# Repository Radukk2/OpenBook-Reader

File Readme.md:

# OpenBook Reader - Project
Block Chart : Block_chart.png file in the root of the directory

Bill of Materials : The bill of materials file can be found at /Manufacturing/Bom.csv

Hardware description
1. Microcontroller - ESP32-C6-WROOM-1-N8
    CPU: 32-bit RISC-V single-core @ up to 160MHz
    Memory: 320KB ROM, 512KB HP SRAM, 16KB LP SRAM
    Connectivity: Wi-Fi 6, Bluetooth LE 5.0
    Interfaces: GPIO, SPI, UART, I2C, PWM   
    Operating Voltage: 3.3V

   - The given microcontroller uses the following power modes: 
        When the device is active it consumes from 160 to 260 mA.
        When modem sleeps it ranges from 3 to 20 mA.
        On light the device consumes 0.8 mA.
        In Deep-sleep mode it consumes 10 μA.
        Hibernation modes consumes 2.5 μA.

2. Display Interface 7.5" E-Paper Display
    - Interface: SPI via FPC connector
    - Pins:   EPD_CS: GPIO10
            EPD_DC: GPIO5
            EPD_RST: GPIO23
            EPD_BUSY: GPIO3
            MOSI, SCK: Shared with SD card
            Used pins : Pins.xlsx  provieds the full ecplination

    The reasons why we use ePaper is for: 
                                        - ultra-low power consumption
                                        - excellent sunlight readability
3. Storage Solutions
    - MicroSD Card with the SPI interface.
    - 64MB NOR Flash with the same SPI interface.

4. Real time clocks
    We use a DS3231SN model for its high accuracy, backup supported battery.

5. Power Management
    USB-C Interface 
    MCP73831 - Li-Po Battery Charging that is used for charging

6. Buttons
    There are also 3 buttons: reset, boot and change. These are used for user's interaction with the device.

Used Pins: Described fully in Pins.xlsx

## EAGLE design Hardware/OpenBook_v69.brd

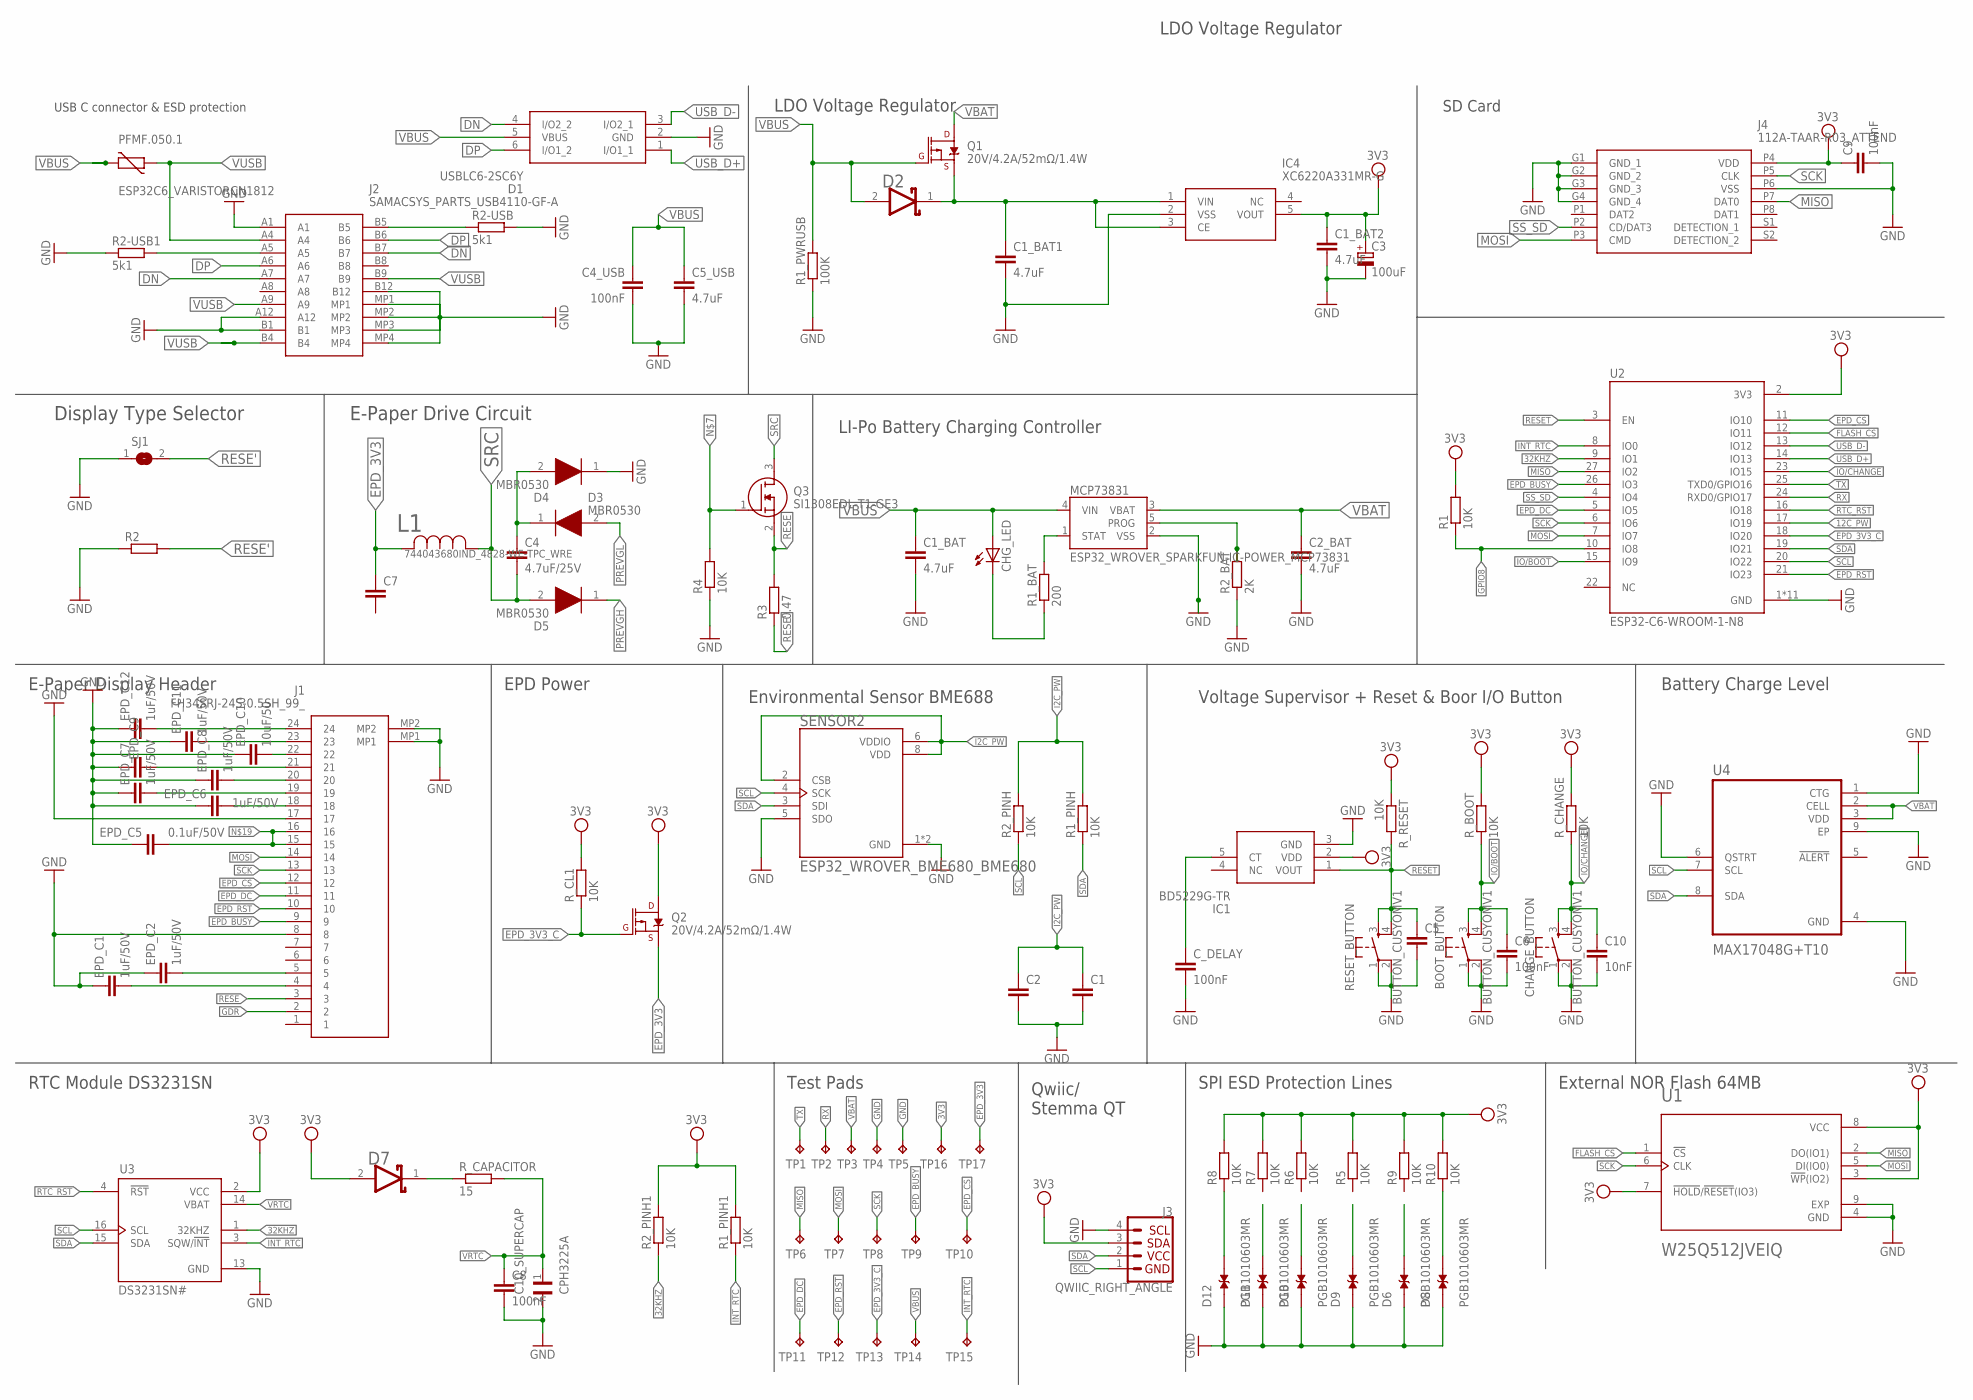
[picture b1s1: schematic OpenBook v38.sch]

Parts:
BOOT_BUTTON: BUTTON_CUSYOMV1; MYBUTTON
C1, C2, C5, C7: EAGLE-LTSPICE_CC0402; EAGLE-LTSPICE_C0402
C1_BAT, C1_BAT1, C1_BAT2, C2_BAT, C5_USB: 4.7uF; EAGLE-LTSPICE_C0402
C3: 100uF; RCL_CT3528
C4: 4.7uF/25V; EAGLE-LTSPICE_C0402
C4_USB, C6, C8, C9: 100nF; EAGLE-LTSPICE_C0402
C10: 10nF; EAGLE-LTSPICE_C0402
C10_SUPERCAP: CPH3225A; CAPCP3225X100N
CHANGE_BUTTON: BUTTON_CUSYOMV1; MYBUTTON
CHG_LED: ADAFRUIT_LEDCHIP-LED0603; ADAFRUIT_CHIP-LED0603
C_DELAY: 100nF; EAGLE-LTSPICE_C0402
D1: USBLC6-2SC6Y; SOT95P280X145-6N
D2, D7: ESP32_WROVER_AVX---SD0805S020S1R0_AVX_SD0805S020S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; ESP32_WROVER_AVX---SD0805S020S1R0_AVX_SD0805S020S1R0_0
D3, D4, D5: MBR0530; SOD3716X135N
D6, D8, D9, D10, D11, D12: PGB1010603MR; DIOC1608X36N
EPD_C1, EPD_C2, EPD_C6, EPD_C7, EPD_C8, EPD_C11, EPD_C12: 1uF/50V; EAGLE-LTSPICE_C0402
EPD_C5: 0.1uF/50V; EAGLE-LTSPICE_C0402
EPD_C9: EAGLE-LTSPICE_CC0402; EAGLE-LTSPICE_C0402
EPD_C10: 10uF/50; EAGLE-LTSPICE_C0402
IC1: BD5229G-TR; SOT95P280X125-5N
IC4: XC6220A331MR-G; SOT95P280X120-5N
J1: FH34SRJ-24S-0.5SH_99_; FH34SRJ24S05SH99
J2: SAMACSYS_PARTS_USB4110-GF-A; SAMACSYS_PARTS_USB4110GFA
J3: QWIIC_RIGHT_ANGLE; JST04_1MM_RA
J4: 112A-TAAR-R03_ATTEND; 112ATAARR03ATTEND
L1: 744043680IND_4828-WE-TPC_WRE; IND_4828-WE-TPC_WRE
MCP73831: ESP32_WROVER_SPARKFUN-IC-POWER_MCP73831; ESP32_WROVER_SPARKFUN-IC-POWER_SOT23-5
PFMF.050.1: ESP32C6_VARISTORCN1812; ESP32C6_VARISTOR_CT/CN1812
Q1, Q2: 20V/4.2A/52mΩ/1.4W; ESP32_WROVER_SPARKFUN-DISCRETESEMI_SOT23-3
Q3: SI1308EDL-T1-GE3; SOT65P210X110-3N
R1, R1_PINH, R1_PINH1, R2_PINH, R2_PINH1, R4, R5, R6, R7, R8, R9, R10: 10K; ESP32_WROVER_EAGLE-LTSPICE_R0402
R1_BAT: 200; ESP32_WROVER_EAGLE-LTSPICE_R0402
R1_PWRUSB: 100K; ESP32_WROVER_EAGLE-LTSPICE_R0402
R2: ESP32_WROVER_EAGLE-LTSPICE_RR0402; ESP32_WROVER_EAGLE-LTSPICE_R0402
R2-USB, R2-USB1: 5k1; ESP32_WROVER_EAGLE-LTSPICE_R0402
R2_BAT: 2K; ESP32_WROVER_EAGLE-LTSPICE_R0402
R3: 0.47; ESP32_WROVER_EAGLE-LTSPICE_R0402
RESET_BUTTON: BUTTON_CUSYOMV1; MYBUTTON
R_BOOT: 10K; ESP32_WROVER_EAGLE-LTSPICE_R0402
R_CAPACITOR: 15; ESP32_WROVER_EAGLE-LTSPICE_R0402
R_CHANGE: 10K; ESP32_WROVER_EAGLE-LTSPICE_R0402
R_CL1: 10K; ESP32_WROVER_EAGLE-LTSPICE_R0402
R_RESET: 10K; ESP32_WROVER_EAGLE-LTSPICE_R0402
SENSOR2: ESP32_WROVER_BME680_BME680; ESP32_WROVER_BME680_PSON80P300X300X100-8N
SJ1: SJ
TP1, TP2, TP3, TP4, TP5, TP6, TP7, TP8, TP9, TP10, TP11, TP12, TP13, TP14, TP15, TP16, TP17: TPTP20R; TP20R
U1: W25Q512JVEIQ; SON127P600X800X80-9N
U2: ESP32-C6-WROOM-1-N8; XCVR_ESP32-C6-WROOM-1-N8
U3: DS3231SN#; SOIC127P1032X265-16N
U4: MAX17048G+T10; SON50P200X200X80-9N

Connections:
3V3: C1_BAT2.1, C3.+, C9.1, D7.2 (ANODE), IC1.2 (VDD), IC4.5 (VOUT), J3.3, J4.P4 (VDD), Q2.3 (D), R1.2, R1_PINH1.2, R2_PINH1.2, R5.2, R6.2, R7.2, R8.2, R9.2, R10.2, R_BOOT.2, R_CHANGE.2, R_CL1.2, R_RESET.1, TP16.TP, U1.3 (!WP!(IO2)), U1.7 (!HOLD!/!RESET!(IO3)), U1.8 (VCC), U2.2 (3V3), U3.2 (VCC)
12C_PW: U2.17 (IO19)
32KHZ: R2_PINH1.1, U2.9 (IO1), U3.1 (32KHZ)
DN: D1.4 (I/O2_2), J2.A7, J2.B7
DP: D1.6 (I/O1_2), J2.A6, J2.B6
EPD_3V3: C7.1, L1.2, Q2.2 (S), TP17.TP
EPD_3V3_C: Q2.1 (G), R_CL1.1, TP13.TP, U2.18 (IO20)
EPD_BUSY: J1.9, TP9.TP, U2.26 (IO3)
EPD_CS: J1.12, TP10.TP, U2.11 (IO10)
EPD_DC: J1.11, TP11.TP, U2.5 (IO5)
EPD_RST: J1.10, TP12.TP, U2.21 (IO23)
FLASH_CS: U1.1 (!CS), U2.12 (IO11)
GDR: J1.2
GND: BOOT_BUTTON.1, BOOT_BUTTON.2, C1.2, C1_BAT.2, C1_BAT1.2, C1_BAT2.2, C2.2, C2_BAT.2, C3.-, C4_USB.2, C5.2, C5_USB.2, C6.2, C8.2, C9.2, C10.2, C10_SUPERCAP.2, CHANGE_BUTTON.1, CHANGE_BUTTON.2, C_DELAY.2, D1.2 (GND), D4.1 (K), D6.1, D8.1, D9.1, D10.1, D11.1, D12.1, EPD_C1.1, EPD_C2.1, EPD_C5.1, EPD_C6.1, EPD_C7.1, EPD_C8.1, EPD_C9.1, EPD_C10.1, EPD_C11.1, EPD_C12.1, IC1.3 (GND), IC4.2 (VSS), J1.8, J1.17, J1.MP1, J1.MP2, J2.A1, J2.A12, J2.B1, J2.B12, J2.MP1, J2.MP2, J2.MP3, J2.MP4, J3.4, J4.G1 (GND_1), J4.G2 (GND_2), J4.G3 (GND_3), J4.G4 (GND_4), J4.P6 (VSS), MCP73831.2 (VSS), R1_PWRUSB.1, R2.1, R2-USB.2, R2-USB1.1, R2_BAT.1, R4.1, RESET_BUTTON.1, RESET_BUTTON.2, SENSOR2.1 (GND), SENSOR2.5 (SDO), SENSOR2.7 (GND), SJ1.1, TP4.TP, TP5.TP, U1.4 (GND), U1.9 (EXP), U2.1 (GND), U2.28 (GND), U2.29_1 (GND), U2.29_2 (GND), U2.29_3 (GND), U2.29_4 (GND), U2.29_5 (GND), U2.29_6 (GND), U2.29_7 (GND), U2.29_8 (GND), U2.29_9 (GND), U3.13 (GND), U4.1 (CTG), U4.4 (GND), U4.6 (QSTRT), U4.9 (EP)
GPIO8: R1.1, U2.10 (IO8)
I2C_PW: C1.1, C2.1, R1_PINH.2, R2_PINH.2, SENSOR2.2 (CSB), SENSOR2.6 (VDDIO), SENSOR2.8 (VDD)
INT_RTC: R1_PINH1.1, TP15.TP, U2.8 (IO0), U3.3 (SQW/!INT)
IO/BOOT: BOOT_BUTTON.3, BOOT_BUTTON.4, C6.1, R_BOOT.1, U2.15 (IO9)
IO/CHANGE: C10.1, CHANGE_BUTTON.3, CHANGE_BUTTON.4, R_CHANGE.1, U2.23 (IO15)
MISO: J4.P7 (DAT0), TP6.TP, U1.2 (DO(IO1)), U2.27 (IO2)
MOSI: J1.14, J4.P3 (CMD), TP7.TP, U1.5 (DI(IO0)), U2.7 (IO7)
unnamed: J2.B5, R2-USB.1
unnamed: J2.A5, R2-USB1.2
unnamed: C1_BAT1.1, D2.1 (CATHODE), IC4.1 (VIN), IC4.3 (CE), Q1.2 (S)
unnamed: C4.1, D3.1 (K), D4.2 (A)
unnamed: MCP73831.5 (PROG), R2_BAT.2
unnamed: Q3.1 (G), R4.2
unnamed: EPD_C1.2, J1.4
unnamed: MCP73831.1 (STAT), R1_BAT.2
unnamed: CHG_LED.C, R1_BAT.1
unnamed: EPD_C2.2, J1.5
unnamed: EPD_C6.2, J1.18
unnamed: EPD_C7.2, J1.19
unnamed: EPD_C8.2, J1.20
unnamed: EPD_C9.2, J1.21
unnamed: EPD_C10.2, J1.22
unnamed: EPD_C12.2, J1.24
unnamed: EPD_C11.2, J1.23
unnamed: EPD_C5.2, J1.15, J1.16
unnamed: C_DELAY.1, IC1.5 (CT)
unnamed: D7.1 (CATHODE), R_CAPACITOR.1
unnamed: D12.2, R8.1
unnamed: D8.2, R10.1
PREVGH: D5.1 (K)
PREVGL: D3.2 (A)
RESE: J1.3, Q3.2 (S), R3.2
RESE': R2.2, R3.1, SJ1.2
RESET: C5.1, IC1.1 (VOUT), RESET_BUTTON.3, RESET_BUTTON.4, R_RESET.2, U2.3 (EN)
RTC_RST: U2.16 (IO18), U3.4 (!RST)
RX: TP2.TP, U2.24 (RXD0/GPIO17)
SCK: J1.13, J4.P5 (CLK), TP8.TP, U1.6 (CLK), U2.6 (IO6)
SCL: J3.1, R2_PINH.1, SENSOR2.4 (SCK), U2.20 (IO22), U3.16 (SCL), U4.7 (SCL)
SDA: J3.2, R1_PINH.1, SENSOR2.3 (SDI), U2.19 (IO21), U3.15 (SDA), U4.8 (SDA)
SRC: C4.2, D5.2 (A), L1.1, Q3.3 (D)
SS_SD: J4.P2 (CD/DAT3), U2.4 (IO4)
TX: TP1.TP, U2.25 (TXD0/GPIO16)
USB_D+: D1.1 (I/O1_1), U2.14 (IO13)
USB_D-: D1.3 (I/O2_1), U2.13 (IO12)
VBAT: C2_BAT.1, MCP73831.3 (VBAT), Q1.3 (D), TP3.TP, U4.2 (CELL), U4.3 (VDD)
VBUS: C1_BAT.1, C4_USB.1, C5_USB.1, CHG_LED.A, D1.5 (VBUS), D2.2 (ANODE), MCP73831.4 (VIN), PFMF.050.1.2, Q1.1 (G), R1_PWRUSB.2, TP14.TP
VRTC: C8.1, C10_SUPERCAP.1, R_CAPACITOR.2, U3.14 (VBAT)
VUSB: J2.A4, J2.A9, J2.B4, J2.B9, PFMF.050.1.1

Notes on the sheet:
USB C connector & ESD protection
LDO Voltage Regulator
LDO Voltage Regulator
SD Card
LI-Po Battery Charging Controller
Display Type Selector
E-Paper Drive Circuit
E-Paper Display Header
EPD Power
Environmental Sensor BME688
Voltage Supervisor + Reset & Boor I/O Button
Battery Charge Level
SPI ESD Protection Lines
Qwiic/ Stemma QT
External NOR Flash 64MB
Test Pads
RTC Module DS3231SN

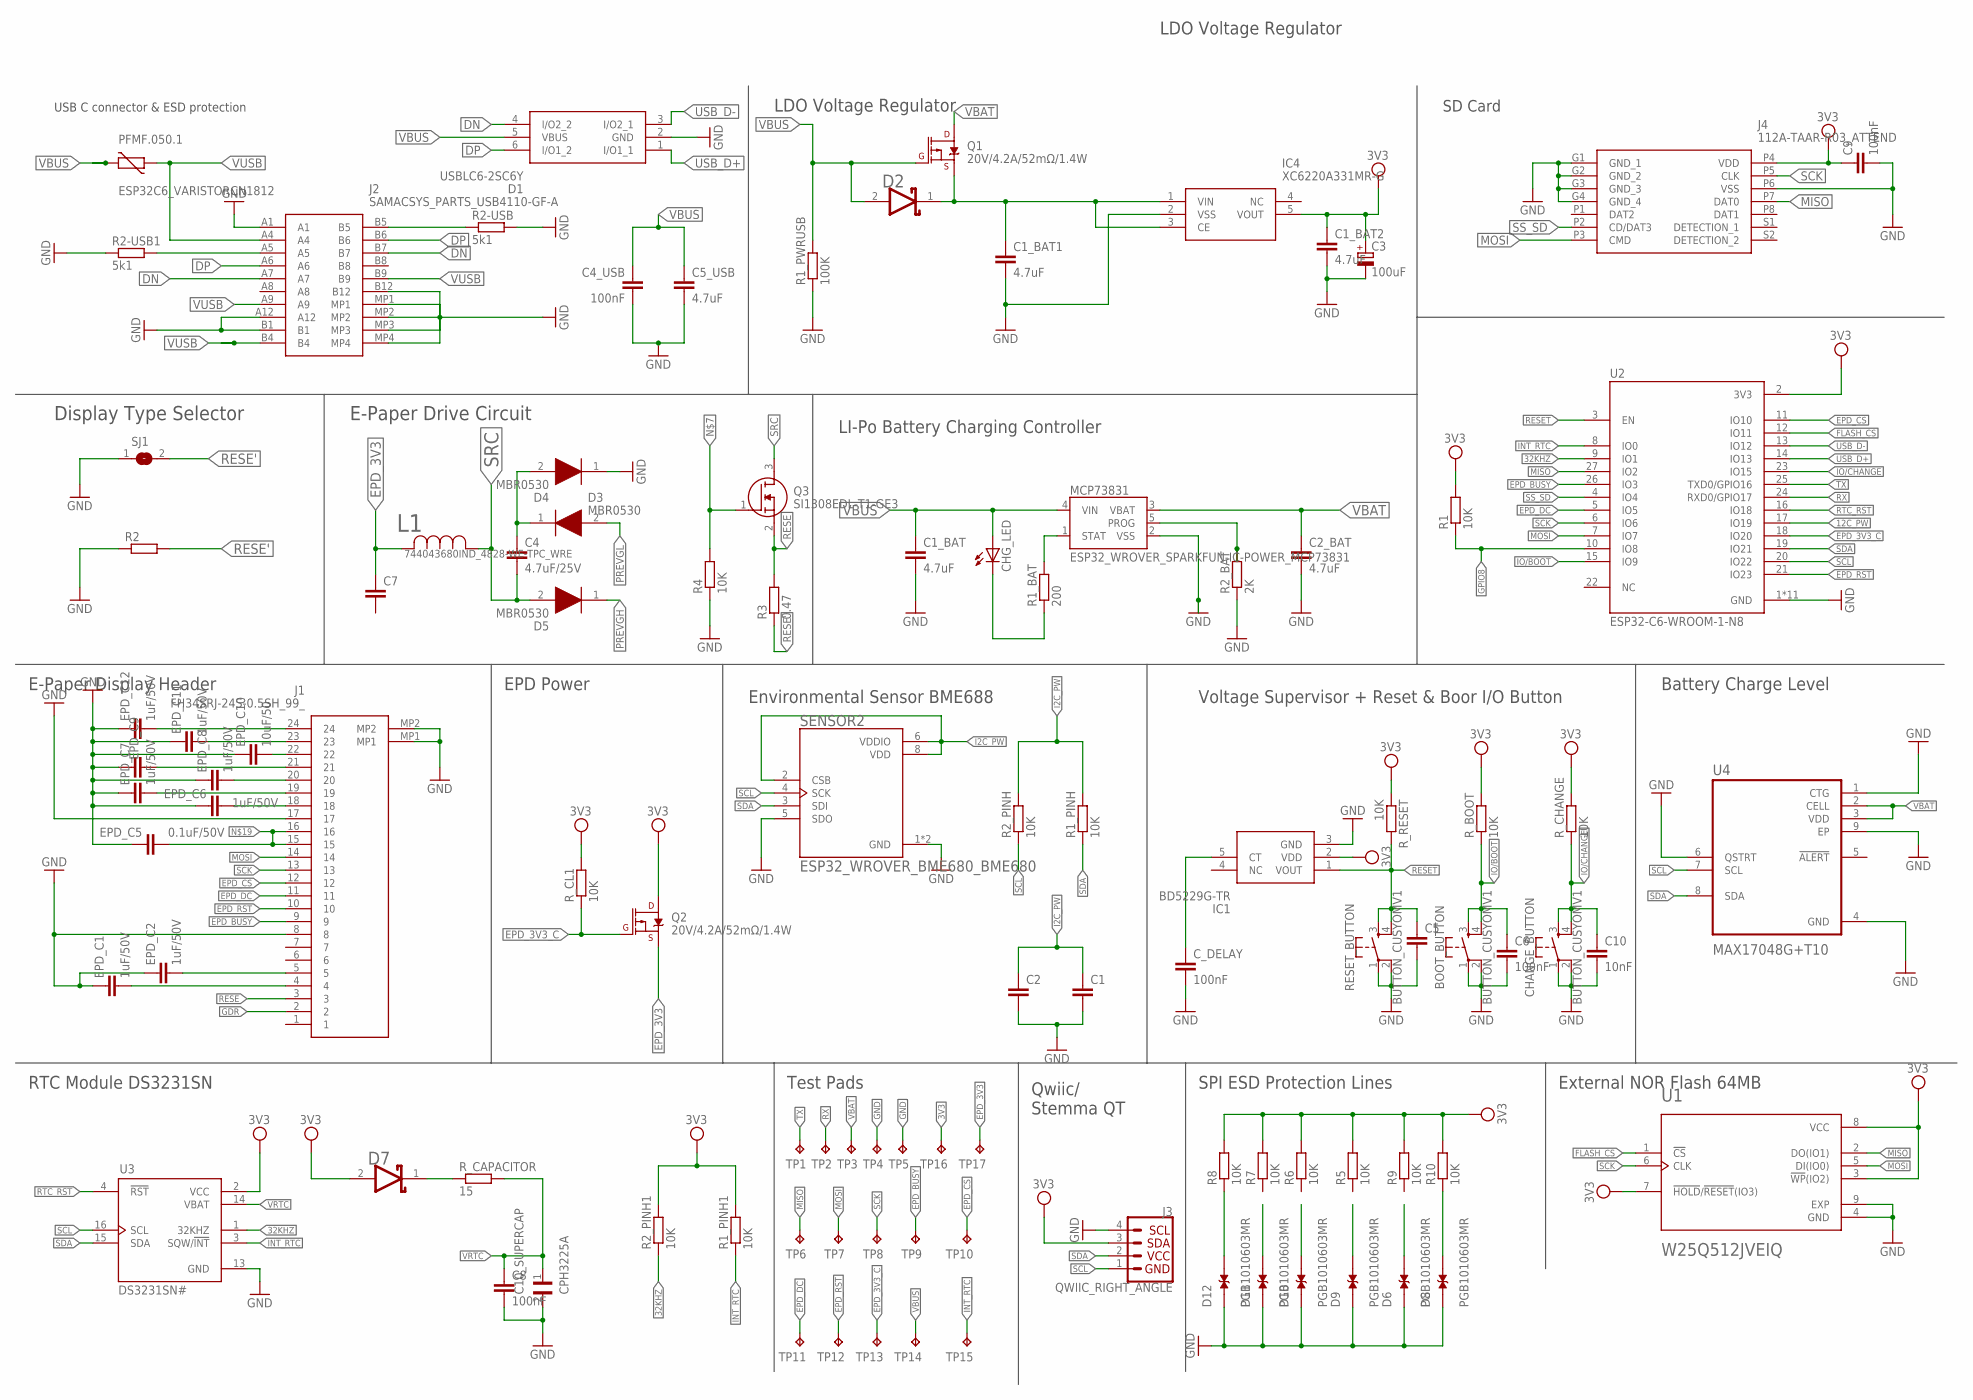
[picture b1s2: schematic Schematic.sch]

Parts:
BOOT_BUTTON: BUTTON_CUSYOMV1; MYBUTTON
C1, C2, C5, C7: EAGLE-LTSPICE_CC0402; EAGLE-LTSPICE_C0402
C1_BAT, C1_BAT1, C1_BAT2, C2_BAT, C5_USB: 4.7uF; EAGLE-LTSPICE_C0402
C3: 100uF; RCL_CT3528
C4: 4.7uF/25V; EAGLE-LTSPICE_C0402
C4_USB, C6, C8, C9: 100nF; EAGLE-LTSPICE_C0402
C10: 10nF; EAGLE-LTSPICE_C0402
C10_SUPERCAP: CPH3225A; CAPCP3225X100N
CHANGE_BUTTON: BUTTON_CUSYOMV1; MYBUTTON
CHG_LED: ADAFRUIT_LEDCHIP-LED0603; ADAFRUIT_CHIP-LED0603
C_DELAY: 100nF; EAGLE-LTSPICE_C0402
D1: USBLC6-2SC6Y; SOT95P280X145-6N
D2, D7: ESP32_WROVER_AVX---SD0805S020S1R0_AVX_SD0805S020S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; ESP32_WROVER_AVX---SD0805S020S1R0_AVX_SD0805S020S1R0_0
D3, D4, D5: MBR0530; SOD3716X135N
D6, D8, D9, D10, D11, D12: PGB1010603MR; DIOC1608X36N
EPD_C1, EPD_C2, EPD_C6, EPD_C7, EPD_C8, EPD_C11, EPD_C12: 1uF/50V; EAGLE-LTSPICE_C0402
EPD_C5: 0.1uF/50V; EAGLE-LTSPICE_C0402
EPD_C9: EAGLE-LTSPICE_CC0402; EAGLE-LTSPICE_C0402
EPD_C10: 10uF/50; EAGLE-LTSPICE_C0402
IC1: BD5229G-TR; SOT95P280X125-5N
IC4: XC6220A331MR-G; SOT95P280X120-5N
J1: FH34SRJ-24S-0.5SH_99_; FH34SRJ24S05SH99
J2: SAMACSYS_PARTS_USB4110-GF-A; SAMACSYS_PARTS_USB4110GFA
J3: QWIIC_RIGHT_ANGLE; JST04_1MM_RA
J4: 112A-TAAR-R03_ATTEND; 112ATAARR03ATTEND
L1: 744043680IND_4828-WE-TPC_WRE; IND_4828-WE-TPC_WRE
MCP73831: ESP32_WROVER_SPARKFUN-IC-POWER_MCP73831; ESP32_WROVER_SPARKFUN-IC-POWER_SOT23-5
PFMF.050.1: ESP32C6_VARISTORCN1812; ESP32C6_VARISTOR_CT/CN1812
Q1, Q2: 20V/4.2A/52mΩ/1.4W; ESP32_WROVER_SPARKFUN-DISCRETESEMI_SOT23-3
Q3: SI1308EDL-T1-GE3; SOT65P210X110-3N
R1, R1_PINH, R1_PINH1, R2_PINH, R2_PINH1, R4, R5, R6, R7, R8, R9, R10: 10K; ESP32_WROVER_EAGLE-LTSPICE_R0402
R1_BAT: 200; ESP32_WROVER_EAGLE-LTSPICE_R0402
R1_PWRUSB: 100K; ESP32_WROVER_EAGLE-LTSPICE_R0402
R2: ESP32_WROVER_EAGLE-LTSPICE_RR0402; ESP32_WROVER_EAGLE-LTSPICE_R0402
R2-USB, R2-USB1: 5k1; ESP32_WROVER_EAGLE-LTSPICE_R0402
R2_BAT: 2K; ESP32_WROVER_EAGLE-LTSPICE_R0402
R3: 0.47; ESP32_WROVER_EAGLE-LTSPICE_R0402
RESET_BUTTON: BUTTON_CUSYOMV1; MYBUTTON
R_BOOT: 10K; ESP32_WROVER_EAGLE-LTSPICE_R0402
R_CAPACITOR: 15; ESP32_WROVER_EAGLE-LTSPICE_R0402
R_CHANGE: 10K; ESP32_WROVER_EAGLE-LTSPICE_R0402
R_CL1: 10K; ESP32_WROVER_EAGLE-LTSPICE_R0402
R_RESET: 10K; ESP32_WROVER_EAGLE-LTSPICE_R0402
SENSOR2: ESP32_WROVER_BME680_BME680; ESP32_WROVER_BME680_PSON80P300X300X100-8N
SJ1: SJ
TP1, TP2, TP3, TP4, TP5, TP6, TP7, TP8, TP9, TP10, TP11, TP12, TP13, TP14, TP15, TP16, TP17: TPTP20R; TP20R
U1: W25Q512JVEIQ; SON127P600X800X80-9N
U2: ESP32-C6-WROOM-1-N8; XCVR_ESP32-C6-WROOM-1-N8
U3: DS3231SN#; SOIC127P1032X265-16N
U4: MAX17048G+T10; SON50P200X200X80-9N

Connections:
3V3: C1_BAT2.1, C3.+, C9.1, D7.2 (ANODE), IC1.2 (VDD), IC4.5 (VOUT), J3.3, J4.P4 (VDD), Q2.3 (D), R1.2, R1_PINH1.2, R2_PINH1.2, R5.2, R6.2, R7.2, R8.2, R9.2, R10.2, R_BOOT.2, R_CHANGE.2, R_CL1.2, R_RESET.1, TP16.TP, U1.3 (!WP!(IO2)), U1.7 (!HOLD!/!RESET!(IO3)), U1.8 (VCC), U2.2 (3V3), U3.2 (VCC)
12C_PW: U2.17 (IO19)
32KHZ: R2_PINH1.1, U2.9 (IO1), U3.1 (32KHZ)
DN: D1.4 (I/O2_2), J2.A7, J2.B7
DP: D1.6 (I/O1_2), J2.A6, J2.B6
EPD_3V3: C7.1, L1.2, Q2.2 (S), TP17.TP
EPD_3V3_C: Q2.1 (G), R_CL1.1, TP13.TP, U2.18 (IO20)
EPD_BUSY: J1.9, TP9.TP, U2.26 (IO3)
EPD_CS: J1.12, TP10.TP, U2.11 (IO10)
EPD_DC: J1.11, TP11.TP, U2.5 (IO5)
EPD_RST: J1.10, TP12.TP, U2.21 (IO23)
FLASH_CS: U1.1 (!CS), U2.12 (IO11)
GDR: J1.2
GND: BOOT_BUTTON.1, BOOT_BUTTON.2, C1.2, C1_BAT.2, C1_BAT1.2, C1_BAT2.2, C2.2, C2_BAT.2, C3.-, C4_USB.2, C5.2, C5_USB.2, C6.2, C8.2, C9.2, C10.2, C10_SUPERCAP.2, CHANGE_BUTTON.1, CHANGE_BUTTON.2, C_DELAY.2, D1.2 (GND), D4.1 (K), D6.1, D8.1, D9.1, D10.1, D11.1, D12.1, EPD_C1.1, EPD_C2.1, EPD_C5.1, EPD_C6.1, EPD_C7.1, EPD_C8.1, EPD_C9.1, EPD_C10.1, EPD_C11.1, EPD_C12.1, IC1.3 (GND), IC4.2 (VSS), J1.8, J1.17, J1.MP1, J1.MP2, J2.A1, J2.A12, J2.B1, J2.B12, J2.MP1, J2.MP2, J2.MP3, J2.MP4, J3.4, J4.G1 (GND_1), J4.G2 (GND_2), J4.G3 (GND_3), J4.G4 (GND_4), J4.P6 (VSS), MCP73831.2 (VSS), R1_PWRUSB.1, R2.1, R2-USB.2, R2-USB1.1, R2_BAT.1, R4.1, RESET_BUTTON.1, RESET_BUTTON.2, SENSOR2.1 (GND), SENSOR2.5 (SDO), SENSOR2.7 (GND), SJ1.1, TP4.TP, TP5.TP, U1.4 (GND), U1.9 (EXP), U2.1 (GND), U2.28 (GND), U2.29_1 (GND), U2.29_2 (GND), U2.29_3 (GND), U2.29_4 (GND), U2.29_5 (GND), U2.29_6 (GND), U2.29_7 (GND), U2.29_8 (GND), U2.29_9 (GND), U3.13 (GND), U4.1 (CTG), U4.4 (GND), U4.6 (QSTRT), U4.9 (EP)
GPIO8: R1.1, U2.10 (IO8)
I2C_PW: C1.1, C2.1, R1_PINH.2, R2_PINH.2, SENSOR2.2 (CSB), SENSOR2.6 (VDDIO), SENSOR2.8 (VDD)
INT_RTC: R1_PINH1.1, TP15.TP, U2.8 (IO0), U3.3 (SQW/!INT)
IO/BOOT: BOOT_BUTTON.3, BOOT_BUTTON.4, C6.1, R_BOOT.1, U2.15 (IO9)
IO/CHANGE: C10.1, CHANGE_BUTTON.3, CHANGE_BUTTON.4, R_CHANGE.1, U2.23 (IO15)
MISO: J4.P7 (DAT0), TP6.TP, U1.2 (DO(IO1)), U2.27 (IO2)
MOSI: J1.14, J4.P3 (CMD), TP7.TP, U1.5 (DI(IO0)), U2.7 (IO7)
unnamed: J2.B5, R2-USB.1
unnamed: J2.A5, R2-USB1.2
unnamed: C1_BAT1.1, D2.1 (CATHODE), IC4.1 (VIN), IC4.3 (CE), Q1.2 (S)
unnamed: C4.1, D3.1 (K), D4.2 (A)
unnamed: MCP73831.5 (PROG), R2_BAT.2
unnamed: Q3.1 (G), R4.2
unnamed: EPD_C1.2, J1.4
unnamed: MCP73831.1 (STAT), R1_BAT.2
unnamed: CHG_LED.C, R1_BAT.1
unnamed: EPD_C2.2, J1.5
unnamed: EPD_C6.2, J1.18
unnamed: EPD_C7.2, J1.19
unnamed: EPD_C8.2, J1.20
unnamed: EPD_C9.2, J1.21
unnamed: EPD_C10.2, J1.22
unnamed: EPD_C12.2, J1.24
unnamed: EPD_C11.2, J1.23
unnamed: EPD_C5.2, J1.15, J1.16
unnamed: C_DELAY.1, IC1.5 (CT)
unnamed: D7.1 (CATHODE), R_CAPACITOR.1
unnamed: D12.2, R8.1
unnamed: D8.2, R10.1
PREVGH: D5.1 (K)
PREVGL: D3.2 (A)
RESE: J1.3, Q3.2 (S), R3.2
RESE': R2.2, R3.1, SJ1.2
RESET: C5.1, IC1.1 (VOUT), RESET_BUTTON.3, RESET_BUTTON.4, R_RESET.2, U2.3 (EN)
RTC_RST: U2.16 (IO18), U3.4 (!RST)
RX: TP2.TP, U2.24 (RXD0/GPIO17)
SCK: J1.13, J4.P5 (CLK), TP8.TP, U1.6 (CLK), U2.6 (IO6)
SCL: J3.1, R2_PINH.1, SENSOR2.4 (SCK), U2.20 (IO22), U3.16 (SCL), U4.7 (SCL)
SDA: J3.2, R1_PINH.1, SENSOR2.3 (SDI), U2.19 (IO21), U3.15 (SDA), U4.8 (SDA)
SRC: C4.2, D5.2 (A), L1.1, Q3.3 (D)
SS_SD: J4.P2 (CD/DAT3), U2.4 (IO4)
TX: TP1.TP, U2.25 (TXD0/GPIO16)
USB_D+: D1.1 (I/O1_1), U2.14 (IO13)
USB_D-: D1.3 (I/O2_1), U2.13 (IO12)
VBAT: C2_BAT.1, MCP73831.3 (VBAT), Q1.3 (D), TP3.TP, U4.2 (CELL), U4.3 (VDD)
VBUS: C1_BAT.1, C4_USB.1, C5_USB.1, CHG_LED.A, D1.5 (VBUS), D2.2 (ANODE), MCP73831.4 (VIN), PFMF.050.1.2, Q1.1 (G), R1_PWRUSB.2, TP14.TP
VRTC: C8.1, C10_SUPERCAP.1, R_CAPACITOR.2, U3.14 (VBAT)
VUSB: J2.A4, J2.A9, J2.B4, J2.B9, PFMF.050.1.1

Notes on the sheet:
USB C connector & ESD protection
LDO Voltage Regulator
LDO Voltage Regulator
SD Card
LI-Po Battery Charging Controller
Display Type Selector
E-Paper Drive Circuit
E-Paper Display Header
EPD Power
Environmental Sensor BME688
Voltage Supervisor + Reset & Boor I/O Button
Battery Charge Level
SPI ESD Protection Lines
Qwiic/ Stemma QT
External NOR Flash 64MB
Test Pads
RTC Module DS3231SN

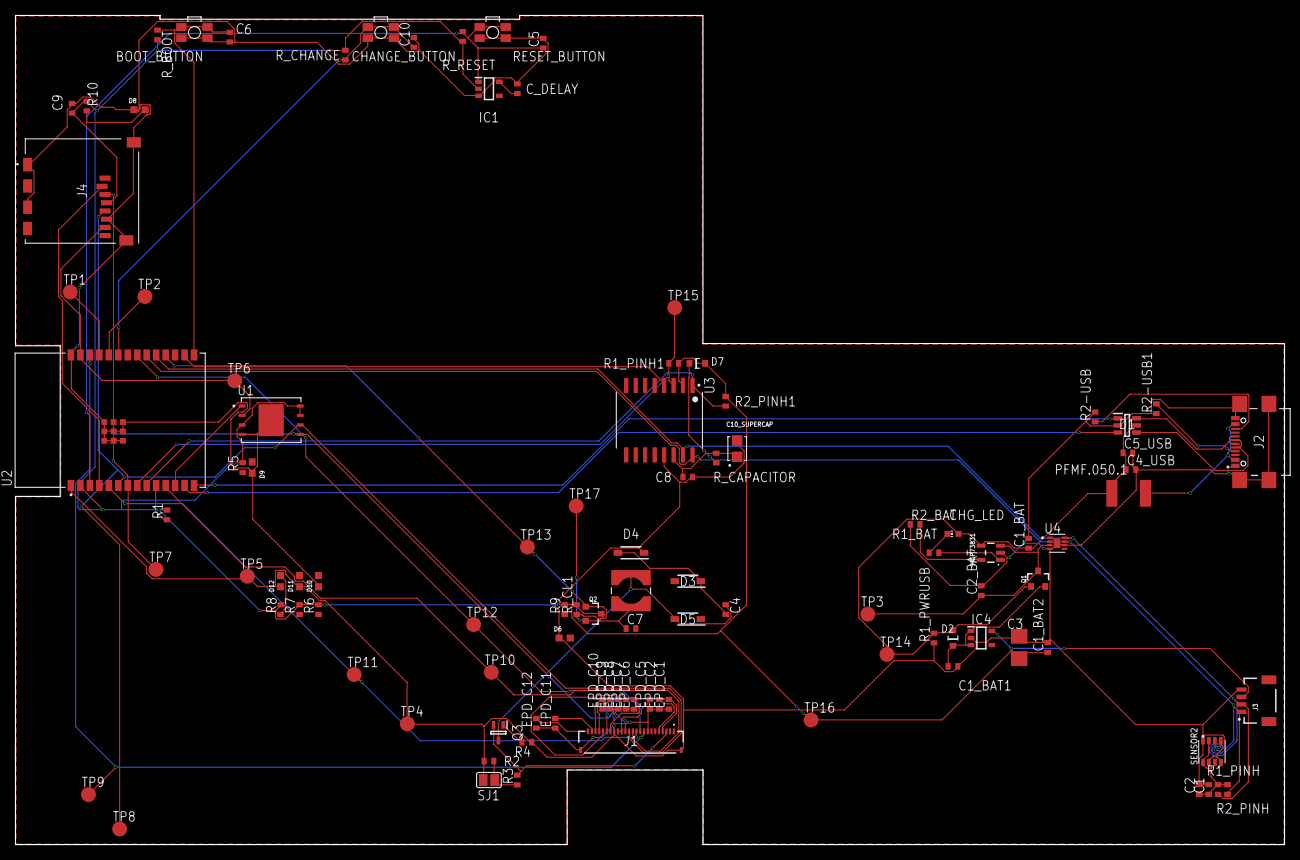
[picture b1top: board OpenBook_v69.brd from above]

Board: 2 copper layers, 170.2 x 111.2 mm, 103 parts (0 on the bottom side), 58 nets.

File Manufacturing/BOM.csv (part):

Qty,Value,Device,Package,Parts,Description,ARROW_PART_NUMBER,ARROW_PRICE-STOCK,AVAILABILITY,CENTROID_NOT_SPECIFIED,CHECK_PRICES,COPYRIGHT,DATASHEET,DESCRIPTION,DIGIKEY_DESCRIPTION,DIGIKEY_PART_NUMBER,HEIGHT,LEAD_FREE,MANUFACTURER_NAME,MANUFACTURER_PART_NUMBER,MF,MFR_NAME,MOUSER_PART_NUMBER,MOUSER_PRICE-STOCK,MOUSER_TESTING_PART_NUMBER,MOUSER_TESTING_PRICE-STOCK,MP,MPN,PACKAGE,POPULARITY,PREFIX,PRICE,PROD_ID,PURCHASE-URL,ROHS,SNAPEDA_LINK,SPICEMODEL,SPICEPREFIX,TEMPERATURE_RANGE_HIGH,TEMPERATURE_RANGE_LOW,TP_SIGNAL_NAME,VALUE
1,,ADAFRUIT_LEDCHIP-LED0603,ADAFRUIT_CHIP-LED0603,CHG_LED,LED,,,,,,,,,,,,,,,,,,,,,,,,,,,,,,,,,,,,
5,,EAGLE-LTSPICE_CC0402,EAGLE-LTSPICE_C0402,"C1, C2, C5, C7, EPD_C9","CAPACITOR, European symbol",,,,,,,,,,,,,,,,,,,,,,,,,,,,,,,NONE,C,,,,
1,,ESP32_WROVER_EAGLE-LTSPICE_RR0402,ESP32_WROVER_EAGLE-LTSPICE_R0402,R2,"RESISTOR, European symbol",,,,,,,,,,,,,,,,,,,,,,,,,,,,,,,NONE,R,,,,
1,,SJ,SJ,SJ1,SMD solder JUMPER,,,,,,,,,,,,,,,,,,,,,,,,3,,,,,,,,,,,,
1,0.1uF/50V,EAGLE-LTSPICE_CC0402,EAGLE-LTSPICE_C0402,EPD_C5,"CAPACITOR, European symbol",,,,,,,,,,,,,,,,,,,,,,,,,,,,,,,NONE,C,,,,
1,0.47,ESP32_WROVER_EAGLE-LTSPICE_RR0402,ESP32_WROVER_EAGLE-LTSPICE_R0402,R3,"RESISTOR, European symbol",,,,,,,,,,,,,,,,,,,,,,,,,,,,,,,NONE,R,,,,
1,100K,ESP32_WROVER_EAGLE-LTSPICE_RR0402,ESP32_WROVER_EAGLE-LTSPICE_R0402,R1_PWRUSB,"RESISTOR, European symbol",,,,,,,,,,,,,,,,,,,,,,,,,,,,,,,NONE,R,,,,
5,100nF,EAGLE-LTSPICE_CC0402,EAGLE-LTSPICE_C0402,"C4_USB, C6, C8, C9, C_DELAY","CAPACITOR, European symbol",,,,,,,,,,,,,,,,,,,,,,,,,,,,,,,NONE,C,,,,
1,100uF,RCL_CPOL-EUCT3528,RCL_CT3528,C3,"POLARIZED CAPACITOR, European symbol",,,,,,,,,,,,,,,,,,,,,,,,0,,,,,,,,C,,,,
16,10K,ESP32_WROVER_EAGLE-LTSPICE_RR0402,ESP32_WROVER_EAGLE-LTSPICE_R0402,"R1, R1_PINH, R1_PINH1, R2_PINH, R2_PINH1, R4, R5, R6, R7, R8, R9, R10, R_BOOT, R_CHANGE, R_CL1, R_RESET","RESISTOR, European symbol",,,,,,,,,,,,,,,,,,,,,,,,,,,,,,,NONE,R,,,,
1,10nF,EAGLE-LTSPICE_CC0402,EAGLE-LTSPICE_C0402,C10,"CAPACITOR, European symbol",,,,,,,,,,,,,,,,,,,,,,,,,,,,,,,NONE,C,,,,
1,10uF/50,EAGLE-LTSPICE_CC0402,EAGLE-LTSPICE_C0402,EPD_C10,"CAPACITOR, European symbol",,,,,,,,,,,,,,,,,,,,,,,,,,,,,,,NONE,C,,,,
1,112A-TAAR-R03_ATTEND,112A-TAAR-R03_ATTEND,112ATAARR03ATTEND,J4,"Micro SD Card Socket, Push-Push Type, Top Mount, SMT, H=1.83mm, 10u",,,,,,,,Micro SD Card Socket, Push-Push Type, Top Mount, SMT, H=1.83mm, 10u,,,1.9mm,,ATTEND,112A-TAAR-R03 ATTEND,,,,,,,,,,,,,,,,,
1,15,ESP32_WROVER_EAGLE-LTSPICE_RR0402,ESP32_WROVER_EAGLE-LTSPICE_R0402,R_CAPACITOR,"RESISTOR, European symbol",,,,,,,,,,,,,,,,,,,,,,,,,,,,,,,NONE,R,,,,
7,1uF/50V,EAGLE-LTSPICE_CC0402,EAGLE-LTSPICE_C0402,"EPD_C1, EPD_C2, EPD_C6, EPD_C7, EPD_C8, EPD_C11, EPD_C12","CAPACITOR, European symbol",,,,,,,,,,,,,,,,,,,,,,,,,,,,,,,NONE,C,,,,
1,200,ESP32_WROVER_EAGLE-LTSPICE_RR0402,ESP32_WROVER_EAGLE-LTSPICE_R0402,R1_BAT,"RESISTOR, European symbol",,,,,,,,,,,,,,,,,,,,,,,,,,,,,,,NONE,R,,,,
2,20V/4.2A/52mO/1.4W,ESP32_WROVER_SPARKFUN-DISCRETESEMI_MOSFET_PCH-DMG2305UX-7,ESP32_WROVER_SPARKFUN-DISCRETESEMI_SOT23-3,"Q1, Q2",P-channel MOSFETs,,,,,,,,,,,,,,,,,,,,,,,,,,,TRAN-14388,,,,,,,,,20V/4.2A/52mO/1.4W
1,2K,ESP32_WROVER_EAGLE-LTSPICE_RR0402,ESP32_WROVER_EAGLE-LTSPICE_R0402,R2_BAT,"RESISTOR, European symbol",,,,,,,,,,,,,,,,,,,,,,,,,,,,,,,NONE,R,,,,
5,4.7uF,EAGLE-LTSPICE_CC0402,EAGLE-LTSPICE_C0402,"C1_BAT, C1_BAT1, C1_BAT2, C2_BAT, C5_USB","CAPACITOR, European symbol",,,,,,,,,,,,,,,,,,,,,,,,,,,,,,,NONE,C,,,,
1,4.7uF/25V,EAGLE-LTSPICE_CC0402,EAGLE-LTSPICE_C0402,C4,"CAPACITOR, European symbol",,,,,,,,,,,,,,,,,,,,,,,,,,,,,,,NONE,C,,,,
2,5k1,ESP32_WROVER_EAGLE-LTSPICE_RR0402,ESP32_WROVER_EAGLE-LTSPICE_R0402,"R2-USB, R2-USB1","RESISTOR, European symbol",,,,,,,,,,,,,,,,,,,,,,,,,,,,,,,NONE,R,,,,
1,744043680IND_4828-WE-TPC_WRE,744043680IND_4828-WE-TPC_WRE,IND_4828-WE-TPC_WRE,L1,,,,,,,Copyright (C) 2024 Ultra Librarian. All rights reserved.,,,,,,,,744043680,,Wurth Electronics,,,,,,,,,,,,,,,,,,,,
1,BD5229G-TR,BD5229G-TR,SOT95P280X125-5N,IC1,"Voltage Detector with Adjustable Delay Time: CMOS processes are utilized to develop high precision, low current consumption CMOS reset ICs that allow arbitrary setting of the delay time. The extensive lineup includes both Nch Open Drain and CMOS output types in a wide range of detection voltages (from 2.3V to 6.0V, in 0.1V steps), enabling selection of the ideal solution based on customer requirements. In addition, the entire series is of course both lead-free and RoHS-compliant.",,,,,,,,Voltage Detector with Adjustable Delay Time: CMOS processes are utilized to develop high precision, low current consumption CMOS reset ICs that allow arbitrary setting of the delay time. The extensive lineup includes both Nch Open Drain and CMOS output types in a wide range of detection voltages (from 2.3V to 6.0V, in 0.1V steps), enabling selection of the ideal solution based on customer requirements. In addition, the entire series is of course both lead-free and RoHS-compliant.,,,1.25mm,,ROHM Semiconductor,BD5229G-TR,,,755-BD5229G-TR,https://www.mouser.co.uk/ProductDetail/ROHM-Semiconductor/BD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,,,,,,,,,,,,,,
3,BUTTON_CUSYOMV1,BUTTON_CUSYOMV1,MYBUTTON,"BOOT_BUTTON, CHANGE_BUTTON, RESET_BUTTON",,,,,,,,,,,,,,,,,,,,,,,,,,,,,,,,,,,,,
1,CPH3225A,CPH3225A,CAPCP3225X100N,C10_SUPERCAP,Cap 0.011F 3.3V 1210 Flat Check availability,,,Not in stock,,https://www.snapeda.com/parts/CPH3225A/Seiko+Instruments/vie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,,, 11 mF (EDLC) Supercapacitor 3.3 V 1210 (3225 Metric) - - ,,,,,,,Seiko Instruments,,,,,,CPH3225A,,1210 Seiko,,,None,,https://www.snapeda.com/api/url_track_click_mouser/?unipart_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 Instruments&part_name=CPH3225A&search_term=None,,https://www.snapeda.com/parts/CPH3225A/Seiko+Instruments/vie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,,,,,,
1,DS3231SN#,DS3231SN#,SOIC127P1032X265-16N,U3,Real Time Clock Serial 16-Pin SOIC W T/R     Check availability,,,In Stock,,https://www.snapeda.com/parts/DS3231SN%23/Analog+Devices/vie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,,, Extremely Accurate I²C-Integrated RTC/TCXO/Crystal ,,,,,,,Analog Devices,,,,,,DS3231SN#,,SOIC-16 Maxim,,,None,,https://www.snapeda.com/api/url_track_click_mouser/?unipart_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 Devices&part_name=DS3231SN#&search_term=None,,https://www.snapeda.com/parts/DS3231SN%23/Analog+Devices/vie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,,,,,,
1,ESP32-C6-WROOM-1-N8,ESP32-C6-WROOM-1-N8,XCVR_ESP32-C6-WROOM-1-N8,U2,Check availability,,,In Stock,,https://www.snapeda.com/parts/ESP32-C6-WROOM-1-N8/Espressif+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,,, Multiprotocol Modules ESP32-C6 module, Wi-Fi 6 in 2.4 GHz band, Bluetooth 5, Zigbee 3.0 and Thread. ESP34-WROOM Compatible - ENGINEERING SAMPLE ,,,,,,,Espressif Systems,,,,,,ESP32-C6-WROOM-1-N8,,None,,,None,,,,https://www.snapeda.com/parts/ESP32-C6-WROOM-1-N8/Espressif+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,,,
1,ESP32C6_VARISTORCN1812,ESP32C6_VARISTORCN1812,ESP32C6_VARISTOR_CT/CN1812,PFMF.050.1,VARISTOR,,,,,,,,,,,,,,,,,,,,,,,,0,,,,,,,,,,,,
2,ESP32_WROVER_AVX---SD0805S020S1R0_AVX_SD0805S020S1R0_0_0AVX_SD0805S020S1R0_0_0,ESP32_WROVER_AVX---SD0805S020S1R0_AVX_SD0805S020S1R0_0_0AVX_SD0805S020S1R0_0_0,ESP32_WROVER_AVX---SD0805S020S1R0_AVX_SD0805S020S1R0_0,"D2, D7",Schottky Barrier Rectifier Diode,,,,No,,,http://datasheets.avx.com/schottky.pdf,,DIODE SCHOTTKY 20V 1A 0805,478-7800-1-ND,,yes,,,AVX,,581-SD0805S020S1R0,,,,,,0805 (2012 metric),,D,,,,yes,,,,+125°C,-55°C,,
1,ESP32_WROVER_BME680_BME680,ESP32_WROVER_BME680_BME680,ESP32_WROVER_BME680_PSON80P300X300X100-8N,SENSOR2,Integrated Environmental Unit,,,Unavailable,,,,, Integrated Environmental Unit ,,,,,,,Bosch Sensortec,,,,,,BME680,,LGA-8 Bosch Tools,,,None,,,,,,,,,,
1,ESP32_WROVER_SPARKFUN-IC-POWER_MCP73831,ESP32_WROVER_SPARKFUN-IC-POWER_MCP73831,ESP32_WROVER_SPARKFUN-IC-POWER_SOT23-5,MCP73831,"MCP73831T Li-Ion, Li-Pol Controller",,,,,,,,,,,,,,,,,,,,,,,,,,,IC-09995,,,,,,,,,
1,FH34SRJ-24S-0.5SH_99_,FH34SRJ-24S-0.5SH_99_,FH34SRJ24S05SH99,J1," (0.50mm) Surface Mount, Right Angle",,,,,,,,24 Position FFC, FPC Connector Contacts, (0.50mm) Surface Mount, Right Angle,,,1.1mm,,Hirose,FH34SRJ-24S-0.5SH(99),,,798-FH34SRJ24S05SH99,https://www.mouser.co.uk/ProductDetail/Hirose-Connector/FH34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,,,,,,,,,,,,,,,
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
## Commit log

2025-04-06 Licnce and block chart
2025-04-06 all parts
2025-04-06 Images
2025-04-06 Create LICENSE
2025-04-06 rm duplicates

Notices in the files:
parts and their libraries:
DeskAssistant v19 v1: COPYRIGHT: Copyright (C) 2024 Ultra Librarian. All rights reserved.
